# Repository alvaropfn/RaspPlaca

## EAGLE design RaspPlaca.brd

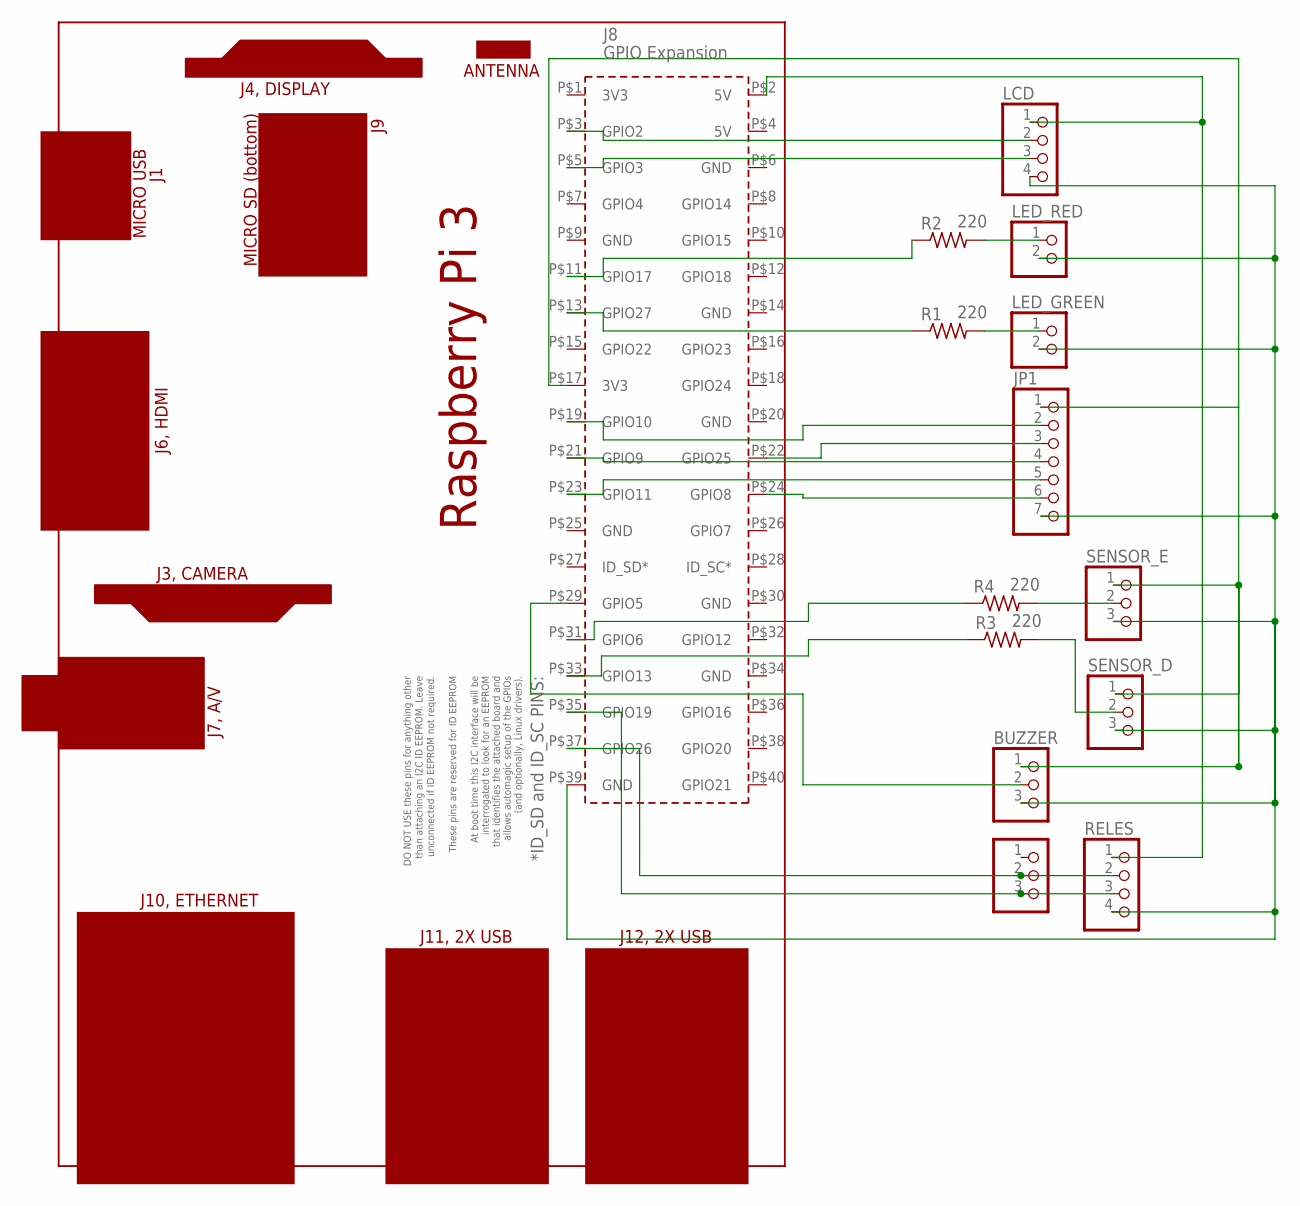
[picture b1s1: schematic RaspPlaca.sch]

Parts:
BUZZER: PINHD-1X3; 1X03
JP1: PINHD-1X7; 1X07
LCD: PINHD-1X4; 1X04
LED_GREEN: PINHD-1X2; 1X02
LED_RED: PINHD-1X2; 1X02
PCB1: RPI3RPI3; RPI3
R1, R2, R3, R4: 220; 0207/10
RELES: PINHD-1X4; 1X04
SENSOR_D: PINHD-1X3; 1X03
SENSOR_E: PINHD-1X3; 1X03
UNIFICADOR_RELES: PINHD-1X3; 1X03

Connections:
3V3: BUZZER.1, JP1.1, PCB1.P$17 (3V3), SENSOR_D.1, SENSOR_E.1
5V: LCD.1, PCB1.P$2 (5V), RELES.1
GND: BUZZER.3, JP1.7, LCD.4, LED_GREEN.2, LED_RED.2, PCB1.P$39 (GND), RELES.4, SENSOR_D.3, SENSOR_E.3
unnamed: JP1.3, PCB1.P$22 (GPIO25)
unnamed: JP1.4, PCB1.P$21 (GPIO9)
unnamed: JP1.6, PCB1.P$24 (GPIO8)
unnamed: JP1.5, PCB1.P$23 (GPIO11)
unnamed: JP1.2, PCB1.P$19 (GPIO10)
unnamed: PCB1.P$31 (GPIO6), R4.1
unnamed: BUZZER.2, PCB1.P$29 (GPIO5)
unnamed: PCB1.P$33 (GPIO13), R3.1
unnamed: LED_GREEN.1, R1.2
unnamed: LED_RED.1, R2.2
unnamed: R3.2, SENSOR_D.2
unnamed: R4.2, SENSOR_E.2
unnamed: PCB1.P$37 (GPIO26), RELES.2, UNIFICADOR_RELES.2
unnamed: PCB1.P$35 (GPIO19), RELES.3, UNIFICADOR_RELES.3
unnamed: LCD.2, PCB1.P$3 (GPIO2)
unnamed: LCD.3, PCB1.P$5 (GPIO3)
unnamed: PCB1.P$13 (GPIO27), R1.1
unnamed: PCB1.P$11 (GPIO17), R2.1

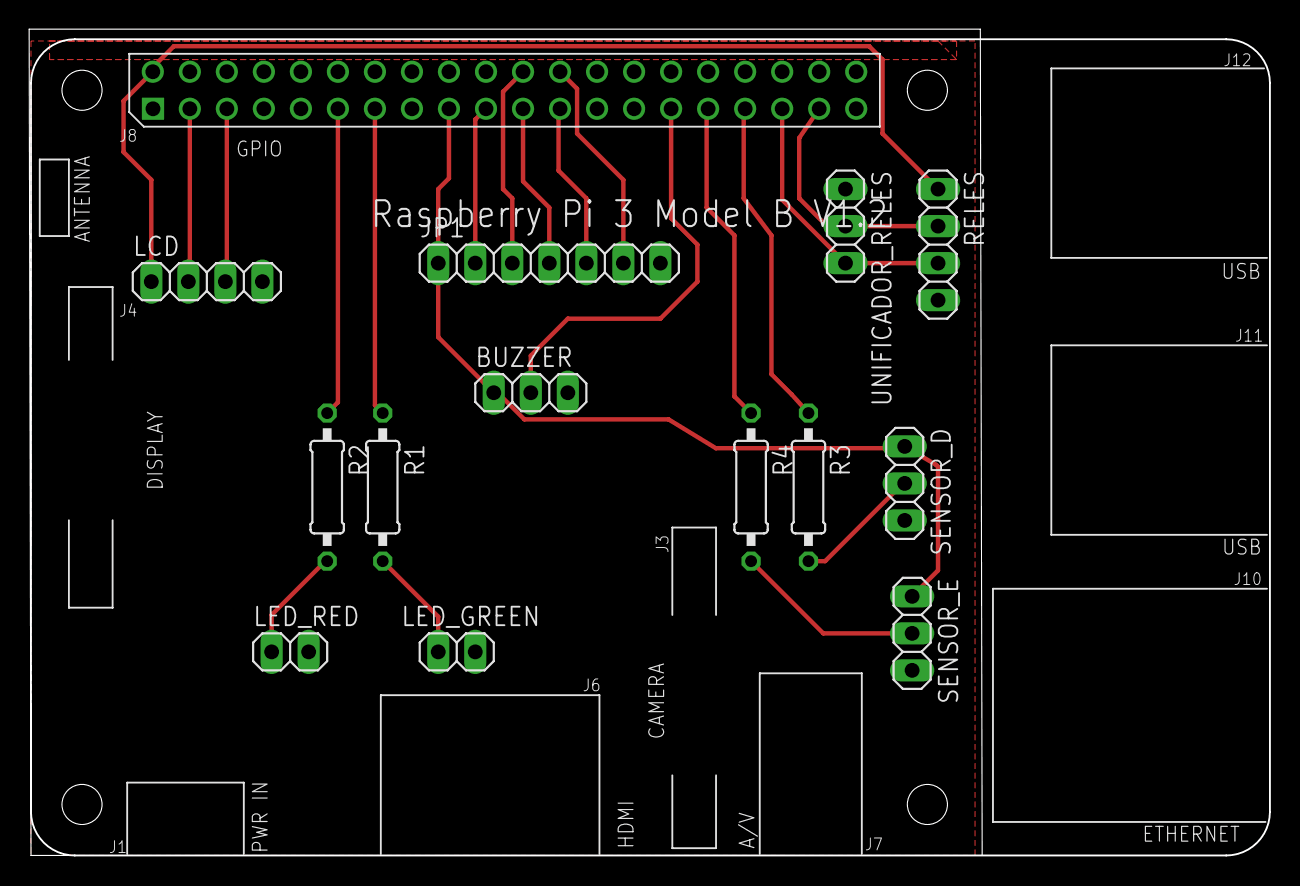
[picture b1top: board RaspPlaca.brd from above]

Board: 2 copper layers, 85.1 x 56.7 mm, 14 parts (0 on the bottom side), 21 nets.
